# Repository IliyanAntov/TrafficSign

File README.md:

<h1 align="center">Пътен знак с дистанционно управление<br/><br/>
 Adjustable traffic sign</h1>

## [Документация](./Documentation/Thesis/Diplomna_rabota_Iliyan_Antov.pdf)

## [Презентация на проекта](https://docs.google.com/presentation/d/1zqneEv3nR7Rzqj332nx1eZqfj7IUzNgIM3qGUmzLu_I/edit?usp=sharing)

*Пътната обстановка се променя постоянно, но знаците, с които обозначаваме правилата, си остават едни и същи. Дипломният проект цели да разреши този проблем - пътният знак с дистанционно управление използва светодиодна матрица, на която могат да се изобразяват произволни предписания според нуждата. Той е свързан към централен сървър с помощта на GPRS връзка, което позволява дистанционното му управление чрез специално разработен управляващ софтуер.*

## Използвани технологии:
* PC application: Python + PyQt5
* Firmware: C/C++ (Arduino)
* MCU platform: AtMega328p + SIM800L
* Schematics/Layout: Altium

## Още снимки:

## Автор:
Илиян Антов - [Iliyan Antov](https://github.com/IliyanAntov) - [i.antov2@gmail.com](i.antov2@gmail.com)

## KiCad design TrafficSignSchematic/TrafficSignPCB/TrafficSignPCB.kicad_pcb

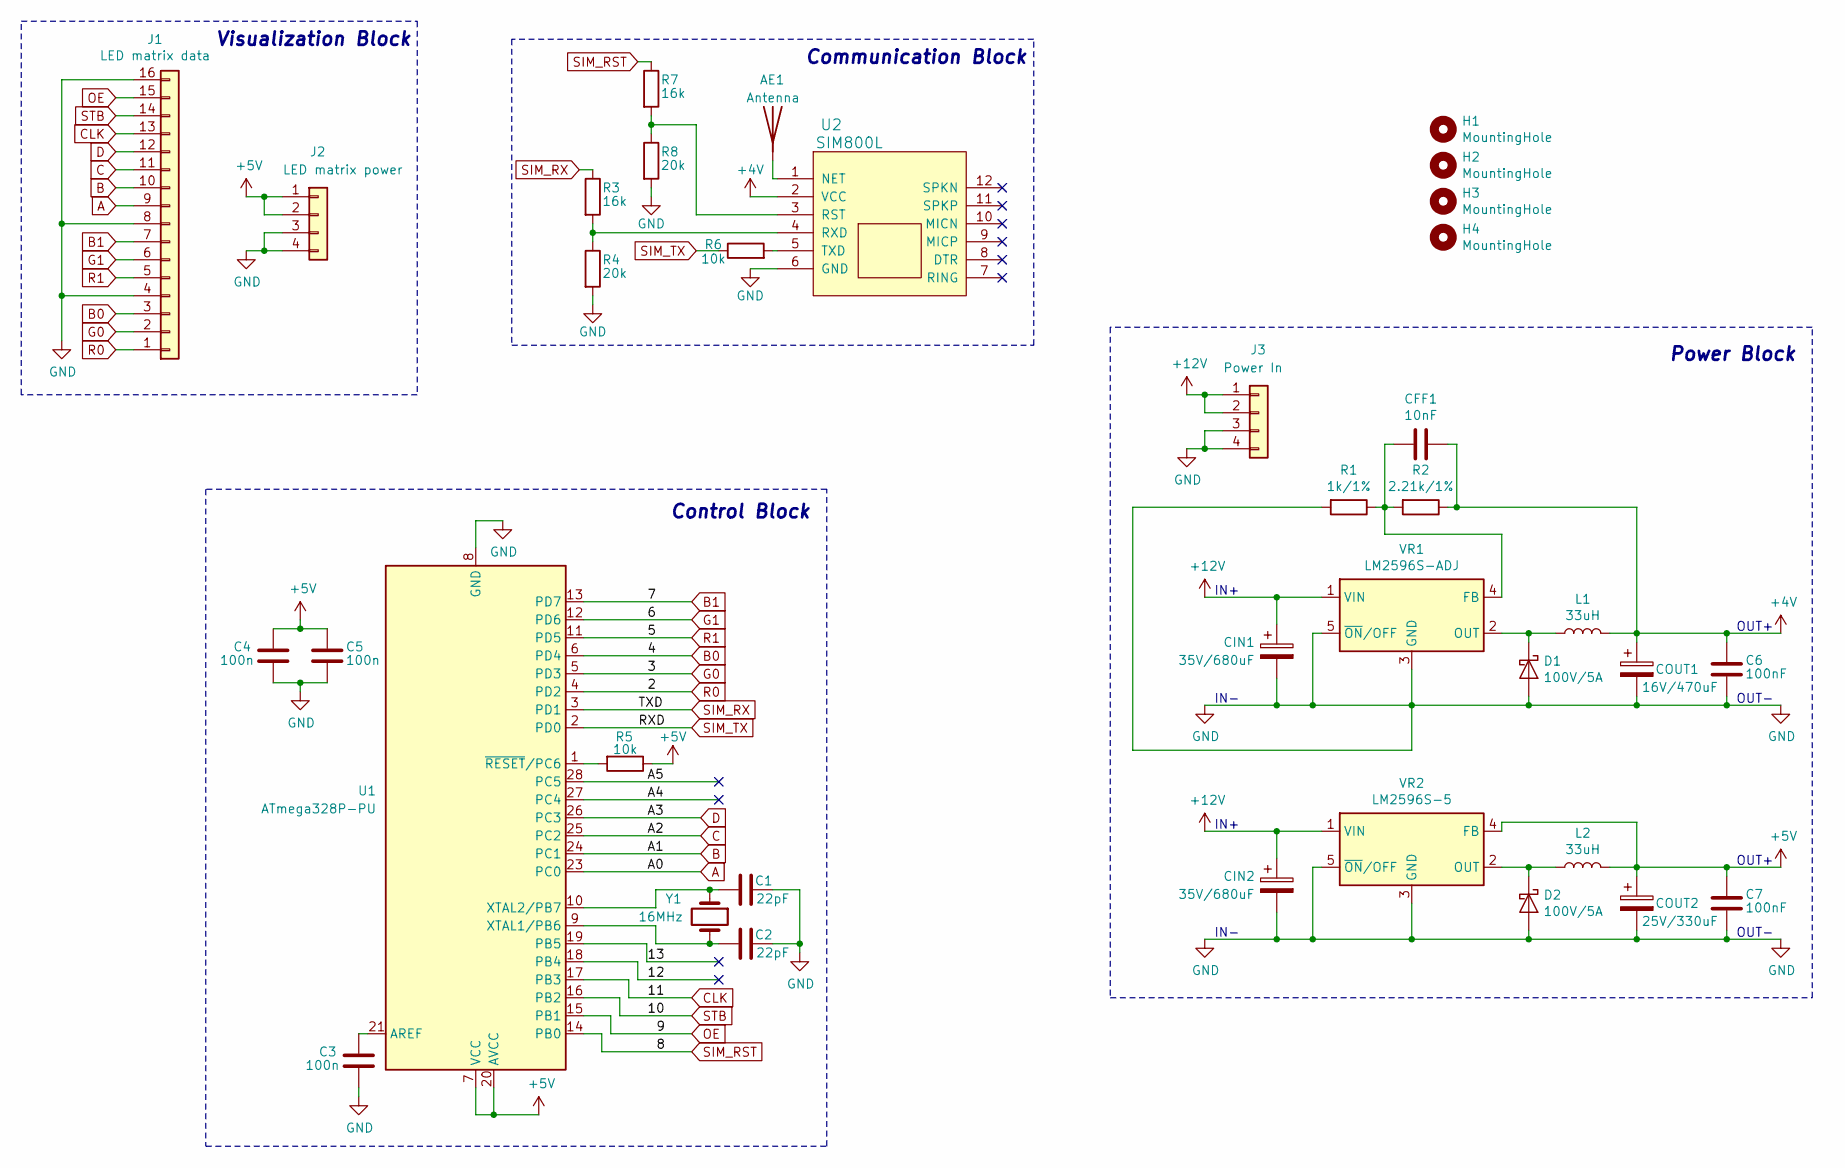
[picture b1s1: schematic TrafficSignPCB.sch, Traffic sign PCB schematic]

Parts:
AE1: Antenna; SMA_Amphenol_901-144_Vertical
C1, C2: 22pF; C_Disc_D4.3mm_W1.9mm_P5.00mm
C3, C4, C5: 100n; C_Disc_D4.3mm_W1.9mm_P5.00mm
C6, C7: 100nF; C_Disc_D4.3mm_W1.9mm_P5.00mm
CFF1: 10nF; C_Disc_D4.3mm_W1.9mm_P5.00mm
CIN1, CIN2: 35V/680uF; CP_Radial_D10.0mm_P5.00mm
COUT1: 16V/470uF; CP_Radial_D8.0mm_P3.50mm
COUT2: 25V/330uF; CP_Radial_D8.0mm_P3.50mm
D1, D2: 100V/5A; D_DO-27_P12.70mm_Horizontal
H1, H2, H3, H4: MountingHole; MountingHole_3.2mm_M3_ISO14580
J1: LED matrix data; IDC-Header_2x08_P2.54mm_Vertical
J2: LED matrix power; Molex_KK-396_A-41791-0004_1x04_P3.96mm_Vertical
J3: Power In; Molex_KK-396_A-41791-0004_1x04_P3.96mm_Vertical
L1, L2: 33uH; L_Bourns_SDR1806
R1: 1k/1%; R_Axial_DIN0207_L6.3mm_D2.5mm_P10.16mm_Horizontal
R2: 2.21k/1%; R_Axial_DIN0207_L6.3mm_D2.5mm_P10.16mm_Horizontal
R3, R7: 16k; R_Axial_DIN0204_L3.6mm_D1.6mm_P7.62mm_Horizontal
R4, R8: 20k; R_Axial_DIN0204_L3.6mm_D1.6mm_P7.62mm_Horizontal
R5, R6: 10k; R_Axial_DIN0204_L3.6mm_D1.6mm_P7.62mm_Horizontal
U1: ATmega328P-PU; DIP-28_W7.62mm
U2: SIM800L; Sim800L
VR1: LM2596S-ADJ; TO-263-5_TabPin3
VR2: LM2596S-5; TO-263-5_TabPin3
Y1: 16MHz; Crystal_HC49-U_Vertical

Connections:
+4V: C6.1, CFF1.1, COUT1.1, L1.2, R2.1, U2.2 (VCC)
+5V: C4.1, C5.1, C7.1, COUT2.1, J2.1, J2.2, L2.2, R5.1, U1.7 (VCC), U1.20 (AVCC), VR2.4 (FB)
+12V: CIN1.1, CIN2.1, J3.1, J3.2, VR1.1 (VIN), VR2.1 (VIN)
/12: U1.18 (PB4)
/13: U1.19 (PB5)
/A4: U1.27 (PC4)
/A5: U1.28 (PC5)
A: J1.9, U1.23 (PC0)
B: J1.10, U1.24 (PC1)
B0: J1.3, U1.6 (PD4)
B1: J1.7, U1.13 (PD7)
C: J1.11, U1.25 (PC2)
CLK: J1.13, U1.17 (PB3)
D: J1.12, U1.26 (PC3)
G0: J1.2, U1.5 (PD3)
G1: J1.6, U1.12 (PD6)
GND: C1.1, C2.1, C3.2, C4.2, C5.2, C6.2, C7.2, CIN1.2, CIN2.2, COUT1.2, COUT2.2, D1.2 (A), D2.2 (A), J1.4, J1.8, J1.16, J2.3, J2.4, J3.3, J3.4, R1.2, R4.2, R8.2, U1.8 (GND), U1.22 (GND), U2.6 (GND), VR1.3 (GND), VR1.5 (~ON~/OFF), VR2.3 (GND), VR2.5 (~ON~/OFF)
unnamed: AE1.1, U2.1 (NET)
unnamed: C1.2, U1.10 (XTAL2/PB7), Y1.1
unnamed: C2.2, U1.9 (XTAL1/PB6), Y1.2
unnamed: C3.1, U1.21 (AREF)
unnamed: CFF1.2, R1.1, R2.2, VR1.4 (FB)
unnamed: D1.1 (K), L1.1, VR1.2 (OUT)
unnamed: D2.1 (K), L2.1, VR2.2 (OUT)
unnamed: R3.2, R4.1, U2.4 (RXD)
unnamed: R5.2, U1.1 (~RESET~/PC6)
unnamed: R6.2, U2.5 (TXD)
unnamed: R7.2, R8.1, U2.3 (RST)
OE: J1.15, U1.15 (PB1)
R0: J1.1, U1.4 (PD2)
R1: J1.5, U1.11 (PD5)
SIM_RST: R7.1, U1.14 (PB0)
SIM_RX: R3.1, U1.3 (PD1)
SIM_TX: R6.1, U1.2 (PD0)
STB: J1.14, U1.16 (PB2)

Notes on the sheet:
IN-
IN+
OUT-
OUT+
Visualization Block
Communication Block
Control Block
Power Block

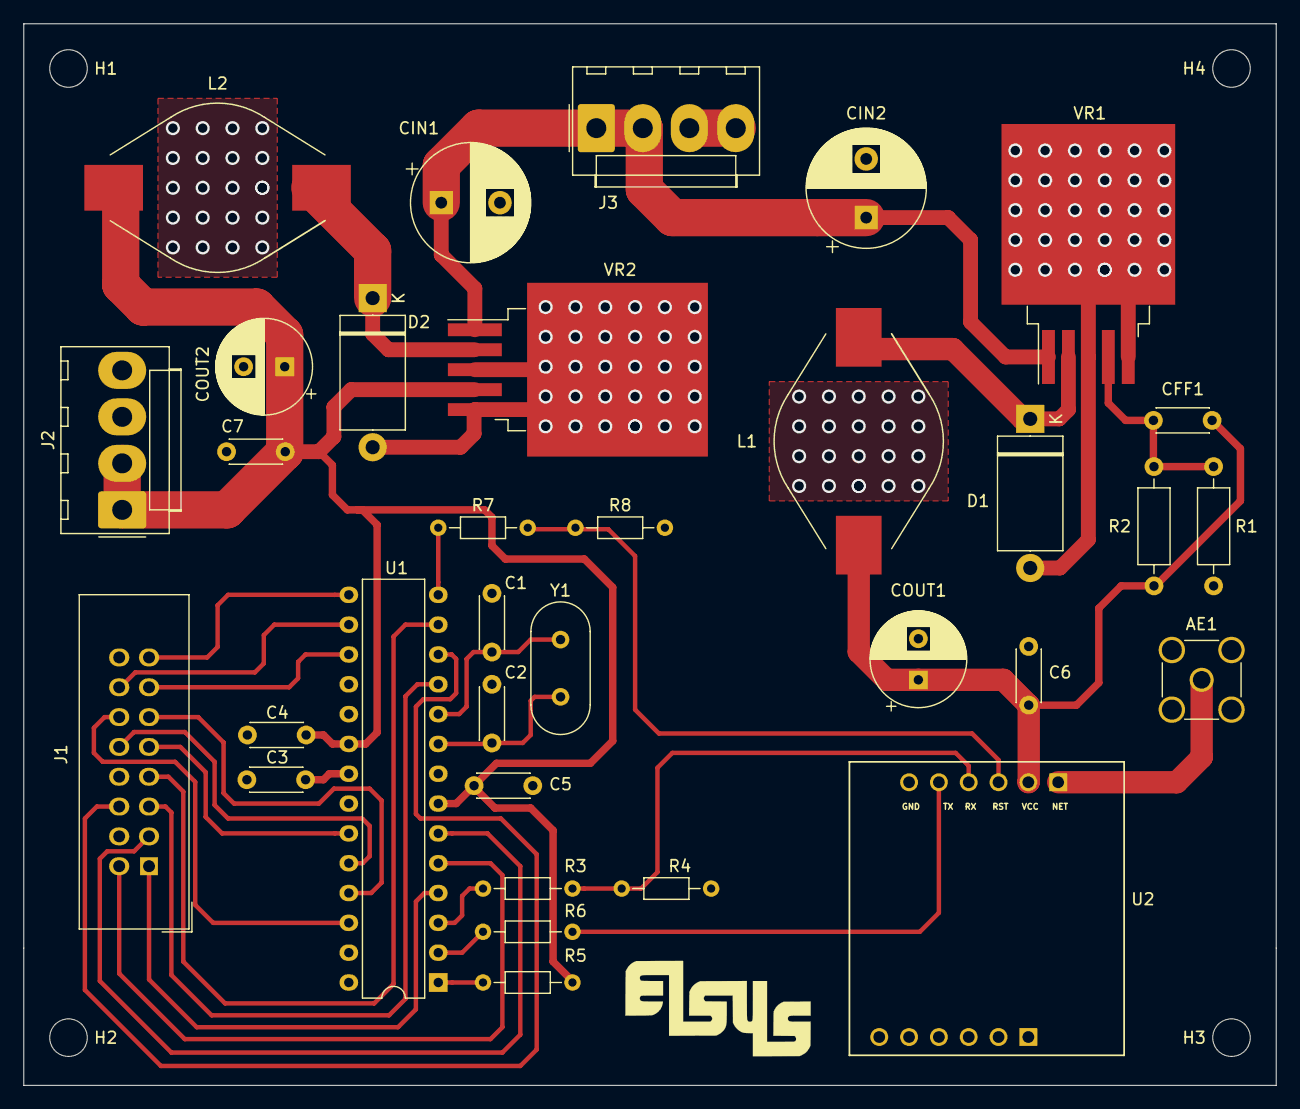
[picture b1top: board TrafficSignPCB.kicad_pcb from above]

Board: 2 copper layers, 106.7 x 90.4 mm, 37 parts (0 on the bottom side), 31 nets.

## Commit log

2019-12-18 Schematic with 12V->4V buck converter
2020-01-09 Full schematic with links to elements
2020-01-13 Code structure
2020-01-14 Test server/client with python sockets
2020-01-15 Simple admin app login form
2020-01-16 Added admin app icon
2020-01-17 Fixed login layout
2020-01-17 Username and passowrd sending and authentication (unsecure)
2020-01-17 Login dialog
2020-01-18 Semi-working retry connection dialog
2020-01-18 Server connection handling and too many connection attempts error
2020-01-18 Server thread listening to client requests
2020-01-18 SIM800L testing code
2020-01-19 Basic admin app UI
2020-01-19 Main page UI and speed limit dialog
2020-01-19 Working speed limit sending
2020-01-19 Speed limit input data validation
2020-01-19 Added footprints to all elements
2020-01-19 PCB elements import
2020-01-20 Placed elements on PCB (Not final)
2020-01-20 Element placement v2
2020-01-20 Router IDC connector
2020-01-20 Router everything
2020-01-20 Added Elsys logo to PCB
2020-01-20 Added dimensions to PCB
2020-01-20 Added schematic PDFs and PCB picture
2020-01-20 Added more PCB images
2020-01-20 Added images folders
2020-01-20 Admin app requesting device list
2020-01-20 Adding to device list
2020-01-21 Added missing capacitors, changed converter output capacitors to Low ESR
2020-01-21 Changed element placement and rerouted board
2020-01-21 Added PCB and schematic images
2020-01-22 Changed buck converter layout
2020-01-23 Moved buck convertors(again)
2020-01-23 Forgot to save...
2020-01-23 Moving elements
2020-01-23 PCB v3
2020-01-23 Added images
2020-01-24 Seperated web server classes
2020-01-24 Semi-working multithreading
2020-01-25 Working admin app multithreading
2020-01-25 Migrated login dialog to Qt designer
2020-01-25 Seperated data exchange classes from main admin app
2020-01-25 Seperated GUI logic from main file
2020-01-25 Device list refresh
2020-01-26 Using TinyGSM library to operate GPRS module
2020-01-26 Traffic sign sending IMEI to server
2020-01-26 Fixed GET and SET request format on admin app and server
2020-01-27 Sending speed limit to device
2020-01-27 Seperated microcontroller code into functions
2020-01-27 Black magic arduino library
2020-01-28 Trying to make serial reading work while visualizing
2020-01-28 Still investigating serial reading while visualizing
2020-01-30 Reworked Adafruit's library to display less colors and thus use less RAM. Now working with TinyGSM
2020-01-30 Fixing set speed limit command
2020-01-31 Working SET command handling
2020-01-31 Fixed speed limit number visualization
2020-02-01 Saving known devices to .yaml file on Admin app
2020-02-01 Added set device alias option to admin app
2020-02-01 Added traffic sign preview images
2020-02-01 Fixed icon in taskbar
2020-02-01 Saving current sign state in uC code
2020-02-01 Added details dialog GUI
2020-02-02 Details button functionality
2020-02-02 Added more traffic signs
2020-02-02 Created set warning dialog GUI
2020-02-02 Working warning signs
2020-02-03 Added stop sign
2020-02-04 Preparing app for AWS deployment
2020-02-04 Changed web server addresses
2020-02-04 Fixed login refusal on too many attempts
2020-02-05 Fixed some exceptions
2020-02-05 More error handling
2020-02-05 Set speed limit error box
2020-02-05 Added SSL to admin connection
2020-02-06 Fixed login dialog
2020-02-06 Added script to generate and save password hashes for users
2020-02-06 Added secure credential check on web server
2020-02-06 Fixed IPs (and a small bug) and deployed to AWS
2020-02-09 Updated full schematic
2020-02-09 Added block diagrams
2020-02-10 Seperated schematic into blocks
2020-02-12 Reordered some stuff and fixed a resistor value
2020-02-13 Removed connector from full schematic power block
2020-02-14 Added an aditional voltage divider
2020-02-14 Cleaned up imports
2020-02-15 Fixed SSL socket creation
2020-02-15 Fixed some bugs and documented some code
2020-02-15 Fixed more bugs and documented more code
2020-02-15 Fixed web server threads
2020-02-15 Changed admin thread handling
2020-02-15 Documenting AdminApp files
2020-02-15 Finished documenting the AdminApp code
2020-02-15 Finished documenting the MicrocontrollerCode
2020-02-16 Finished documenting the WebServer code
2020-02-16 Fixed a small bug in the web server
2020-02-16 Fixed warning sign name bug
2020-02-16 Forgot a bracket
2020-02-16 Added some block schemes and updated the protocol file
2020-02-16 Reorded some code
2020-02-17 Reordered web server file structure
2020-02-17 Fixed a bug in the admin app
2020-02-18 Updated the PCB schematic and layout
2020-02-18 Reordered some code
2020-02-18 Changed the descriptions of some methods
2020-02-18 Made small adjustments to PCB design
2020-02-19 Fixed a bug
2020-02-19 Actually fixed the bug
2020-02-19 Fixed a bug in the GetDevices method of the admin app
2020-02-19 Extened the wait time for traffic sign response
2020-02-19 Extended the timeout period to the server
2020-02-25 Added code block schemes
2020-02-25 Added the projcet's documentation
2020-03-16 Added documentation
2020-05-17 Fixed README
2020-06-06 More readme changes
2025-01-30 README refinements
2025-01-30 Aligned README images
2025-01-30 Centered README heading
